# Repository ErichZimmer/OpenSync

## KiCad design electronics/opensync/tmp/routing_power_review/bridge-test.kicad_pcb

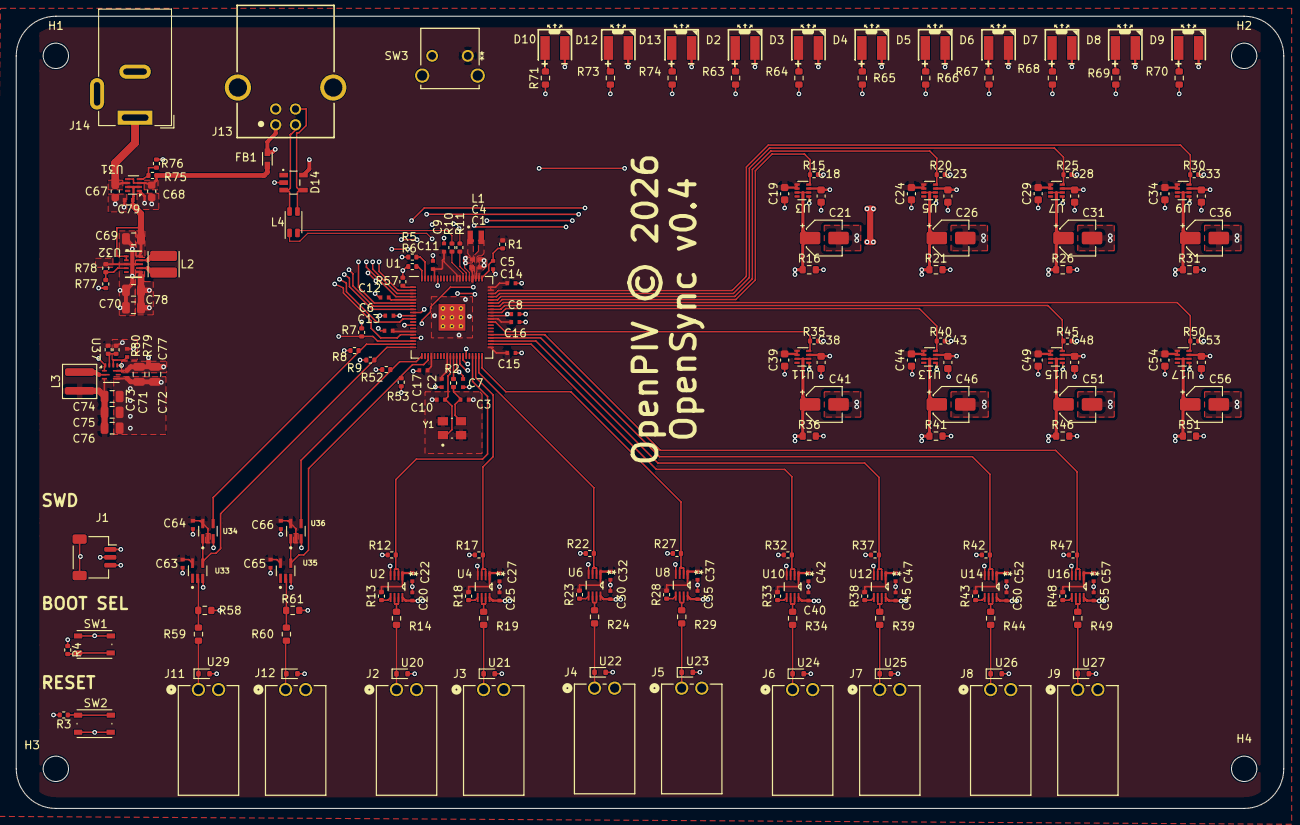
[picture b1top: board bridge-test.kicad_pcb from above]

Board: 4 copper layers, 160.0 x 100.0 mm, 221 parts (0 on the bottom side), 114 nets.

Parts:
C1, C4, C5: 4.7u; C_0402_1005Metric_small_pads
C2, C3: 15p; C_0402_1005Metric_small_pads
C6, C7, C8, C9, C10, C11, C12, C13, C14, C15, C16, C17, C20, C22, C25, C27, C30, C32, C35, C37, C40, C42, C45, C47, C50, C52, C55, C57, C63, C64, C65, C66, C79: 100n; C_0402_1005Metric_small_pads
C18, C19, C23, C24, C28, C29, C33, C34, C38, C39, C43, C44, C48, C49, C53, C54, C67, C68: 1u; C_0603_1608Metric
C21, C26, C31, C36, C41, C46, C51, C56: 22u; CP_Elec_4x5.4
C69, C71, C72: 10u; C_0805_2012Metric
C70, C74, C75, C76, C78: 22u; C_0805_2012Metric
C73: 2.2n; C_0402_1005Metric_small_pads
C77: 470n; C_0402_1005Metric_small_pads
D2, D3, D4, D5, D6, D7, D8, D9, D10, D12, D13: LED; LED-SMD_L4.0-W3.6_A67F-U2BA-1-3A4B-30-R33
D14: 5V; WE-TVS_SOT23-5L
FB1: 0603_W2.6_742792641; FB_Wurth_WE-CBF-0603_W2.6
H1, H2, H3, H4: MountingHole; MountingHole_3.2mm_M3_ISO7380
J1: SM03B-SRSS-TB; JST_SH_SM03B-SRSS-TB_1x03-1MP_P1.00mm_Horizontal
J2, J3, J4, J5, J6, J7, J8, J9, J11, J12: 705530001; CONN_705530001_02_MOL
J13: 61400416121
J14: Barrel_Jack_Switch; BarrelJack_Wuerth_6941xx301002
L1: 3.3u; L_pol_2016
L2: 470n; L_Wuerth_MAPI-3020
L3: 2.2u; L_Wuerth_MAPI-4020
L4: Choke_Wurth_WE-CNSW_744232090; L_CommonMode_Wurth_WE-CNSW-1206
R1: 33; R_0402_1005Metric
R2, R3, R4: 1k; R_0402_1005Metric
R5, R6, R7, R8, R9, R12, R15, R17, R20, R22, R25, R27, R30, R32, R35, R37, R40, R42, R45, R47, R50, R52, R53, R57: 10k; R_0402_1005Metric
R10, R11: 27; R_0402_1005Metric
R13, R18, R23, R28, R33, R38, R43, R48: 47k; R_0402_1005Metric
R14, R19, R24, R29, R34, R39, R44, R49: 39; R_0603_1608Metric
R16, R21, R26, R31, R36, R41, R46, R51, R58, R61: 10k; R_0603_1608Metric
R59, R60: 100; R_0603_1608Metric
R63, R64, R65, R66, R67, R68, R69, R70, R71, R73, R74: 470; R_0603_1608Metric
R75: 301k; R_0402_1005Metric
R76: 100k; R_0402_1005Metric
R77: 806k; R_0402_1005Metric
R78: 91k; R_0402_1005Metric
R79: 4.99k; R_0402_1005Metric
R80: 15.6k; R_0402_1005Metric
SW1, SW2: SW_Push; SW_Push_1P1T_NO_Vertical_Wuerth_434133025816
SW3: 2-1825027-0; SW2_1825027-G_TEC
U1: RP2354_80QFN; RP2350-QFN-80-1EP_10x10_P0.4mm_EP3.4x3.4mm_ThermalVias
U2, U4, U6, U8, U10, U12, U14, U16: SN74LVC2T45DCUR; DCU8
U3, U5, U7, U9, U11, U13, U15, U17, U31: TPS2116DRL; SOT-583-8
U20, U21, U22, U23, U24, U25, U26, U27, U29, U30: TPD1E05U06DYA; D_SOD-523
U32: TPS63802DLAR; DLA0010A
U33, U35: SN74LVC1G17DCKR; SOT65P210X110-5N
U34, U36: 74LVC1G86; SOT65P210X110-5N
U37: TPS62912; Texas_RPU0010A_VQFN-HR-10_2x2mm_P0.5mm
Y1: ABM8-272-T3; XTAL_ABM8-272-T3

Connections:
+1V1: C4.1, C6.1, C7.1, C8.1, L1.1, U1.10 (DVDD), U1.32 (DVDD), U1.51 (DVDD), U1.65 (VREG_FB)
+3V3: C1.1, C9.1, C10.1, C11.1, C12.1, C13.1, C14.1, C15.1, C16.1, C17.1, C19.2, C22.2, C24.2, C27.2, C29.2, C32.2, C34.2, C37.2, C39.2, C42.2, C44.2, C47.2, C49.2, C52.2, C54.2, C57.2, C63.1, C64.1, C65.1, C66.1, C74.2, C75.2, C76.2, L3.2, R1.1, R13.1, R18.1, R23.1, R28.1, R33.1, R38.1, R43.1, R48.1, R80.2, SW3.1, U1.5 (IOVDD), U1.15 (IOVDD), U1.24 (IOVDD), U1.29 (IOVDD), U1.41 (IOVDD), U1.50 (IOVDD), U1.59 (ADC_AVDD), U1.60 (IOVDD), U1.64 (VREG_VIN), U1.68 (USB_OTP_VDD), U1.69 (QSPI_IOVDD), U1.76 (IOVDD), U2.1 (VCCA), U3.5 (MODE), U3.6 (VIN2), U4.1 (VCCA), U5.5 (MODE), U5.6 (VIN2), U6.1 (VCCA), U7.5 (MODE), U7.6 (VIN2), U8.1 (VCCA), U9.5 (MODE), U9.6 (VIN2), U10.1 (VCCA), U11.5 (MODE), U11.6 (VIN2), U12.1 (VCCA), U13.5 (MODE), U13.6 (VIN2), U14.1 (VCCA), U15.5 (MODE), U15.6 (VIN2), U16.1 (VCCA), U17.5 (MODE), U17.6 (VIN2), U33.5 (VCC), U34.2, U34.5 (VCC), U35.5 (VCC), U36.2, U36.5 (VCC), U37.3 (VO)
+5V: C18.2, C23.2, C28.2, C33.2, C38.2, C43.2, C48.2, C53.2, C70.2, C71.2, C72.2, C73.2, C78.2, R77.2, U3.3 (VIN1), U5.3 (VIN1), U7.3 (VIN1), U9.3 (VIN1), U11.3 (VIN1), U13.3 (VIN1), U15.3 (VIN1), U17.3 (VIN1), U32.6 (VOUT), U37.1 (EN/SYNC), U37.6 (VIN), U37.10 (S-CONF)
/IN_G: R53.1, U1.23 (GPIO23), U35.4 (Y), U36.1
/IN_G_INV: R52.1, U1.21 (GPIO21), U36.4
/IN_T: R9.1, U1.20 (GPIO20), U33.4 (Y), U34.1
/IN_T_INV: R8.1, U1.19 (GPIO19), U34.4
/Indicator Panel/BTN_START: R7.1, SW3.2, U1.18 (GPIO18)
/Indicator Panel/LED_A: R70.1, U1.2 (GPIO5)
/Indicator Panel/LED_ACTIVE: R71.1, U1.17 (GPIO17)
/Indicator Panel/LED_B: R69.1, U1.3 (GPIO6)
/Indicator Panel/LED_C: R68.1, U1.4 (GPIO7)
/Indicator Panel/LED_D: R67.1, U1.6 (GPIO8)
/Indicator Panel/LED_E: R66.1, U1.7 (GPIO9)
/Indicator Panel/LED_F: R65.1, U1.8 (GPIO10)
/Indicator Panel/LED_G: R64.1, U1.9 (GPIO11)
/Indicator Panel/LED_GATE: R74.1, U1.13 (GPIO14)
/Indicator Panel/LED_H: R63.1, U1.11 (GPIO12)
/Indicator Panel/LED_TRIG: R73.1, U1.16 (GPIO16)
/Microcontroller Circuitry/QSPI_SS: R4.1, U1.75 (QSPI_SS)
/Microcontroller Circuitry/RUN: SW2.2, U1.35 (RUN)
/Microcontroller Circuitry/SIG_CLOCK: R6.2, U1.80 (GPIO3)
/Microcontroller Circuitry/SIG_GATE_INT: R57.2, U1.1 (GPIO4)
/Microcontroller Circuitry/SIG_T0: R5.2, U1.79 (GPIO2)
/Microcontroller Circuitry/SWCLK: J1.1, U1.33 (SWCLK)
/Microcontroller Circuitry/SWD: J1.3, U1.34 (SWD)
/Microcontroller Circuitry/USB_D+: L4.4, R10.1
/Microcontroller Circuitry/USB_D-: L4.1, R11.1
/Microcontroller Circuitry/VREG_LX: L1.2, U1.63 (VREG_LX)
/Microcontroller Circuitry/XIN: C2.2, U1.30 (XIN), Y1.1
/Microcontroller Circuitry/XOUT: R2.2, U1.31 (XOUT)
/OUT_A: R12.1, U1.37 (GPIO29), U2.2 (A1), U2.3 (A2)
/OUT_B: R17.1, U1.38 (GPIO30), U4.2 (A1), U4.3 (A2)
/OUT_C: R22.1, U1.39 (GPIO31), U6.2 (A1), U6.3 (A2)
/OUT_D: R27.1, U1.40 (GPIO32), U8.2 (A1), U8.3 (A2)
/OUT_E: R32.1, U1.42 (GPIO33), U10.2 (A1), U10.3 (A2)
/OUT_F: R37.1, U1.43 (GPIO34), U12.2 (A1), U12.3 (A2)
/OUT_G: R42.1, U1.44 (GPIO35), U14.2 (A1), U14.3 (A2)
/OUT_H: R47.1, U1.45 (GPIO36), U16.2 (A1), U16.3 (A2)
/Output Channel 1/VOUT: C20.2, C21.1, R16.1, U2.8 (VCCB), U3.2 (VOUT), U3.7 (VOUT)
/Output Channel 2/VOUT: C25.2, C26.1, R21.1, U4.8 (VCCB), U5.2 (VOUT), U5.7 (VOUT)
/Output Channel 3/VOUT: C30.2, C31.1, R26.1, U6.8 (VCCB), U7.2 (VOUT), U7.7 (VOUT)
/Output Channel 4/VOUT: C35.2, C36.1, R31.1, U8.8 (VCCB), U9.2 (VOUT), U9.7 (VOUT)
/Output Channel 5/VOUT: C40.2, C41.1, R36.1, U10.8 (VCCB), U11.2 (VOUT), U11.7 (VOUT)
/Output Channel 6/VOUT: C45.2, C46.1, R41.1, U12.8 (VCCB), U13.2 (VOUT), U13.7 (VOUT)
/Output Channel 7/VOUT: C50.2, C51.1, R46.1, U14.8 (VCCB), U15.2 (VOUT), U15.7 (VOUT)
/Output Channel 8/VOUT: C55.2, C56.1, R51.1, U16.8 (VCCB), U17.2 (VOUT), U17.7 (VOUT)
/Power Interface/VDC: C67.2, J14.1, U31.6 (VIN2)
/Power Interface/VOUT: C69.2, C79.1, U31.2 (VOUT), U31.7 (VOUT), U32.1 (EN), U32.2 (MODE), U32.10 (VIN)
/USB Interface/VBUS_RAW: D14.5 (VDD), FB1.2, J13.1 (VBUS)
/VSEL_A: R15.1, U1.55 (GPIO44_ADC4), U3.4 (PR1)
/VSEL_B: R20.1, U1.56 (GPIO45_ADC5), U5.4 (PR1)
/VSEL_C: R25.1, U1.57 (GPIO46_ADC6), U7.4 (PR1)
/VSEL_D: R30.1, U1.58 (GPIO47_ADC7), U9.4 (PR1)
/VSEL_E: R35.1, U1.49 (GPIO40_ADC0), U11.4 (PR1)
/VSEL_F: R40.1, U1.52 (GPIO41_ADC1), U13.4 (PR1)
/VSEL_G: R45.1, U1.53 (GPIO42_ADC2), U15.4 (PR1)
/VSEL_H: R50.1, U1.54 (GPIO43_ADC3), U17.4 (PR1)
GND: C1.2, C2.1, C3.1, C4.2, C5.2, C6.2, C7.2, C8.2, C9.2, C10.2, C11.2, C12.2, C13.2, C14.2, C15.2, C16.2, C17.2, C18.1, C19.1, C20.1, C21.2, C22.1, C23.1, C24.1, C25.1, C26.2, C27.1, C28.1, C29.1, C30.1, C31.2, C32.1, C33.1, C34.1, C35.1, C36.2, C37.1, C38.1, C39.1, C40.1, C41.2, C42.1, C43.1, C44.1, C45.1, C46.2, C47.1, C48.1, C49.1, C50.1, C51.2, C52.1, C53.1, C54.1, C55.1, C56.2, C57.1, C63.2, C64.2, C65.2, C66.2, C67.1, C68.1, C69.1, C70.1, C71.1, C72.1, C73.1, C74.1, C75.1, C76.1, C77.1, C78.1, C79.2, D2.1 (K), D3.1 (K), D4.1 (K), D5.1 (K), D6.1 (K), D7.1 (K), D8.1 (K), D9.1 (K), D10.1 (K), D12.1 (K), D13.1 (K), D14.2 (GND), J1.2, J1.MP (MountPin), J2.2, J3.2, J4.2, J5.2, J6.2, J7.2, J8.2, J9.2, J11.2, J12.2, J13.4 (GND), J13.S1, J13.S2, J14.3, R3.2, R5.1, R6.1, R7.2, R8.2, R9.2, R12.2, R15.2, R16.2, R17.2, R20.2, R21.2, R22.2, R25.2, R26.2, R27.2, R30.2, R31.2, R32.2, R35.2, R36.2, R37.2, R40.2, R41.2, R42.2, R45.2, R46.2, R47.2, R50.2, R51.2, R52.2, R53.2, R57.1, R58.2, R61.2, R76.2, R78.2, R79.2, SW1.1, U1.62 (VREG_PGND), U1.81 (GND), U2.4 (GND), U3.1 (GND), U4.4 (GND), U5.1 (GND), U6.4 (GND), U7.1 (GND), U8.4 (GND), U9.1 (GND), U10.4 (GND), U11.1 (GND), U12.4 (GND), U13.1 (GND), U14.4 (GND), U15.1 (GND), U16.4 (GND), U17.1 (GND), U20.2 (GND), U21.2 (GND), U22.2 (GND), U23.2 (GND), U24.2 (GND), U25.2 (GND), U26.2 (GND), U27.2 (GND), U29.2 (GND), U30.2 (GND), U31.1 (GND), U32.3 (AGND), U32.8 (GND), U33.3 (GND), U34.3 (GND), U35.3 (GND), U36.3 (GND), U37.4 (PGND), U37.7 (PSNS), Y1.2 (GND), Y1.4 (GND)
unnamed: C3.2, R2.1, Y1.3
unnamed: D2.2 (A), R63.2
unnamed: D3.2 (A), R64.2
unnamed: D4.2 (A), R65.2
unnamed: D5.2 (A), R66.2
unnamed: D6.2 (A), R67.2
unnamed: D7.2 (A), R68.2
unnamed: D8.2 (A), R69.2
unnamed: D9.2 (A), R70.2
unnamed: D10.2 (A), R71.2
unnamed: D12.2 (A), R73.2
unnamed: D13.2 (A), R74.2
unnamed: D14.3 (I/O_1), J13.2 (D-), L4.2
unnamed: D14.4 (I/O_2), J13.3 (D+), L4.3
unnamed: R3.1, SW2.1
unnamed: R4.2, SW1.2
unnamed: R11.2, U1.66 (USB_DM)
unnamed: R10.2, U1.67 (USB_DP)
unnamed: C5.1, R1.2, U1.61 (VREG_AVDD)
unnamed: R14.1, U2.6 (B2), U2.7 (B1)
unnamed: R13.2, U2.5 (DIR)
unnamed: R19.1, U4.6 (B2), U4.7 (B1)
unnamed: R18.2, U4.5 (DIR)
unnamed: R24.1, U6.6 (B2), U6.7 (B1)
unnamed: R23.2, U6.5 (DIR)
unnamed: R29.1, U8.6 (B2), U8.7 (B1)
unnamed: R28.2, U8.5 (DIR)
unnamed: R34.1, U10.6 (B2), U10.7 (B1)
unnamed: R33.2, U10.5 (DIR)
unnamed: R39.1, U12.6 (B2), U12.7 (B1)
unnamed: R38.2, U12.5 (DIR)
unnamed: R44.1, U14.6 (B2), U14.7 (B1)
unnamed: R43.2, U14.5 (DIR)
unnamed: R49.1, U16.6 (B2), U16.7 (B1)
unnamed: R48.2, U16.5 (DIR)
unnamed: J2.1, R14.2, U20.1 (I/O)
unnamed: J3.1, R19.2, U21.1 (I/O)
unnamed: J4.1, R24.2, U22.1 (I/O)
unnamed: J5.1, R29.2, U23.1 (I/O)
unnamed: J6.1, R34.2, U24.1 (I/O)
unnamed: J7.1, R39.2, U25.1 (I/O)
unnamed: J8.1, R44.2, U26.1 (I/O)
unnamed: J9.1, R49.2, U27.1 (I/O)
unnamed: J11.1, R59.1, U29.1 (I/O)
unnamed: J12.1, R60.1, U30.1 (I/O)
unnamed: R75.2, R76.1, U31.4 (PR1)
unnamed: R77.1, R78.1, U32.4 (FB)
unnamed: L2.1, U32.9 (L1)
unnamed: L2.2, U32.7 (L2)
unnamed: R58.1, R59.2, U33.2 (A)
unnamed: R60.2, R61.1, U35.2 (A)
unnamed: R79.1, R80.1, U37.9 (FB)
unnamed: C77.2, U37.8 (NR/SS)
unnamed: L3.1, U37.2 (SW)
VBUS: C68.2, FB1.1, R75.1, U31.3 (VIN1), U31.5 (MODE)

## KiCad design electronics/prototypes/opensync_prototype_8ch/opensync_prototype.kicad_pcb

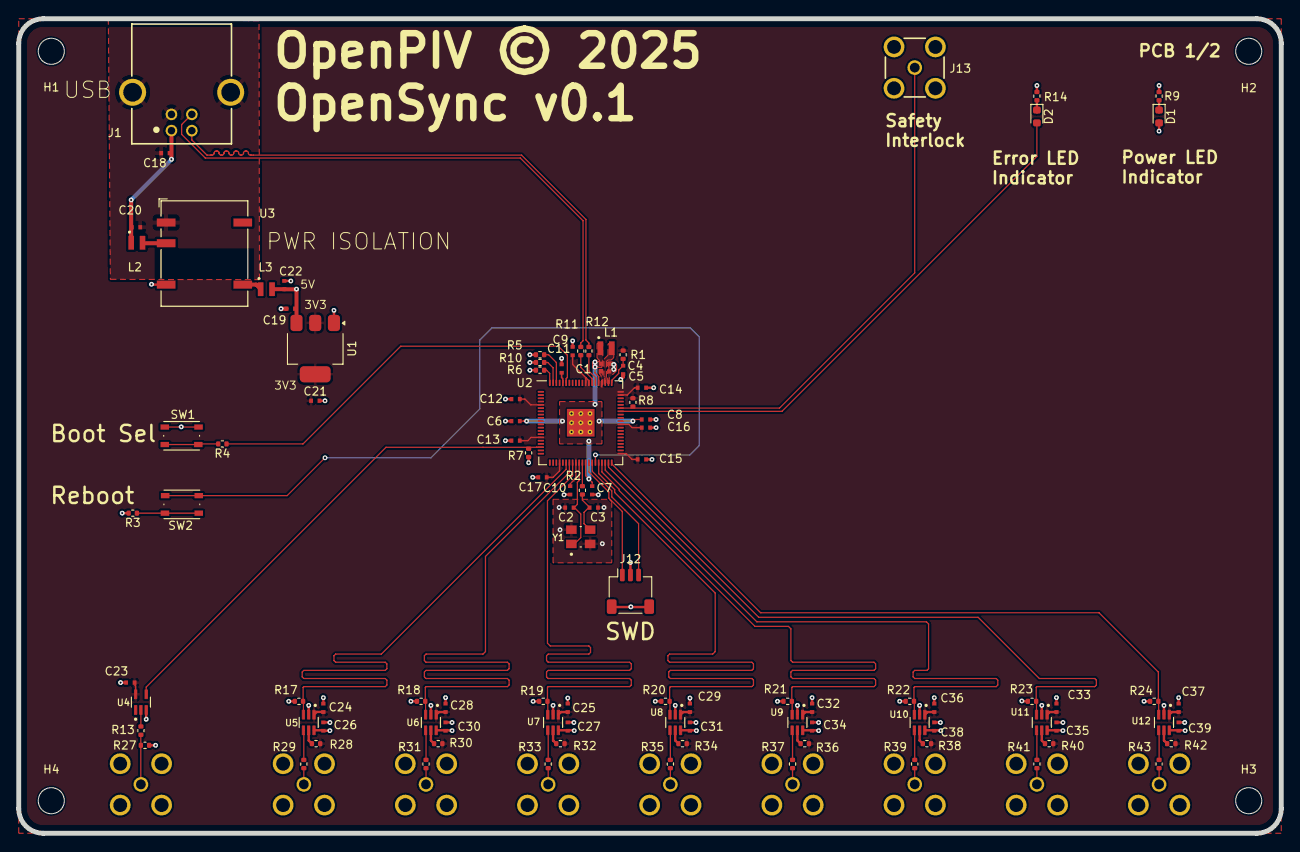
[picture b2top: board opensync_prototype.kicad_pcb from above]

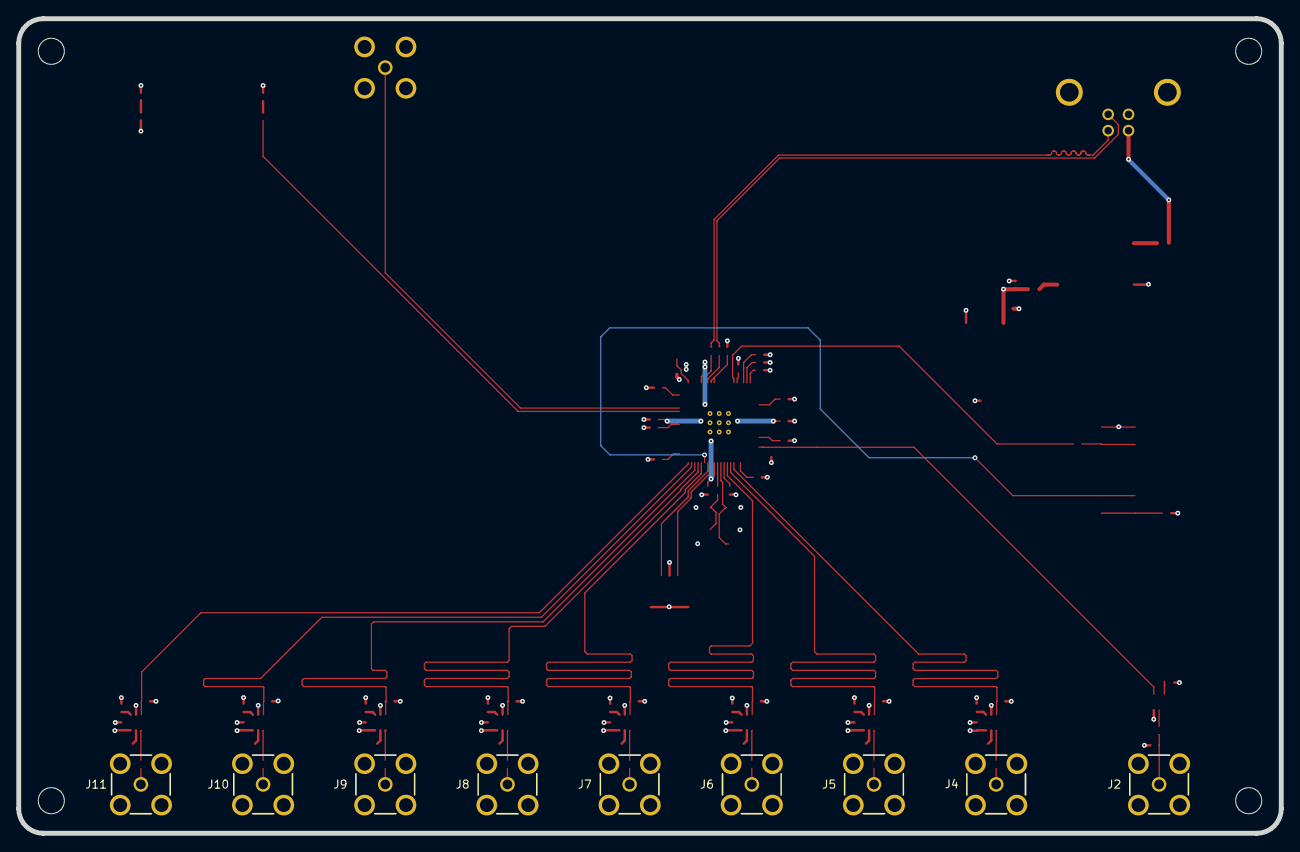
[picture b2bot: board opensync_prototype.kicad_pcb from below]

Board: 4 copper layers, 155.0 x 100.0 mm, 114 parts (9 on the bottom side), 65 nets.

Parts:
C1, C4, C5, C7, C20: 4.7u; C_0402_1005Metric_small_pads
C2, C3: C; C_0402_1005Metric_small_pads
C6, C8, C9, C10, C11, C12, C13, C14, C15, C16, C17, C23, C24, C25, C26, C27, C28, C29, C30, C31, C32, C33, C34, C35, C36, C37, C38, C39: 100n; C_0402_1005Metric_small_pads
C18, C19, C21, C22: 10u; C_0402_1005Metric_small_pads
D1, D2: LED; LED_0603_1608Metric
H1, H2, H3, H4: MountingHole; MountingHole_3.2mm_M3_ISO7380
J1: 61400416121
J2, J4, J5, J6, J7, J8, J9, J10, J11, J13: 61611042121502
J12: SM03B-SRSS-TB; JST_SH_SM03B-SRSS-TB_1x03-1MP_P1.00mm_Horizontal
L1: 3.3u; L_pol_2016
L2: 15u; L_pol_2016
L3: 22u; L_pol_2016
R1: 33; R_0402_1005Metric
R2, R3, R4: 1k; R_0402_1005Metric
R5, R6, R7, R10, R17, R18, R19, R20, R21, R22, R23, R24: 10k; R_0402_1005Metric
R8, R27, R28, R30, R32, R34, R36, R38, R40, R42: 47k; R_0402_1005Metric
R9: 169; R_0402_1005Metric
R11, R12: 27; R_0402_1005Metric
R13: 470; R_0402_1005Metric
R14: 100; R_0402_1005Metric
R29, R31, R33, R35, R37, R39, R41, R43: 49.9; R_0402_1005Metric
SW1, SW2: SW_Push; SW_Push_1P1T_NO_Vertical_Wuerth_434133025816
U1: NCP1117-3.3_SOT223; SOT-223-3_TabPin2
U2: RP2354_80QFN; RP2350-QFN-80-1EP_10x10_P0.4mm_EP3.4x3.4mm_ThermalVias
U3: NXE2S0505MC; Converter_DCDC_Murata_NXExSxxxxMC_SMD
U4: SN74LVC1G17DCKR; SOT65P210X110-5N
U5, U6, U7, U8, U9, U10, U11, U12: SN74LVC1T45DCKR; SOT65P210X110-6N
Y1: ABM8-272-T3; XTAL_ABM8-272-T3

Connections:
+1V1: C4.1, C6.1, C7.1, C8.1, L1.1, U2.10 (DVDD), U2.32 (DVDD), U2.51 (DVDD), U2.65 (VREG_FB)
+3V3: C1.1, C9.1, C10.1, C11.1, C12.1, C13.1, C14.1, C15.1, C16.1, C17.1, C21.1, C23.1, C24.1, C25.1, C28.1, C29.1, C32.1, C33.1, C36.1, C37.1, R1.1, R8.1, R28.1, R30.1, R32.1, R34.1, R36.1, R38.1, R40.1, R42.1, U1.2 (VO), U2.5 (IOVDD), U2.15 (IOVDD), U2.24 (IOVDD), U2.29 (IOVDD), U2.41 (IOVDD), U2.50 (IOVDD), U2.59 (ADC_AVDD), U2.60 (IOVDD), U2.64 (VREG_VIN), U2.68 (USB_OTP_VDD), U2.69 (QSPI_IOVDD), U2.76 (IOVDD), U4.5 (VCC), U5.1 (VCCA), U6.1 (VCCA), U7.1 (VCCA), U8.1 (VCCA), U9.1 (VCCA), U10.1 (VCCA), U11.1 (VCCA), U12.1 (VCCA)
+5V: C19.1, C22.1, C26.1, C27.1, C30.1, C31.1, C34.1, C35.1, C38.1, C39.1, D1.2 (A), L3.2, U1.3 (VI), U5.6 (VCCB), U6.6 (VCCB), U7.6 (VCCB), U8.6 (VCCB), U9.6 (VCCB), U10.6 (VCCB), U11.6 (VCCB), U12.6 (VCCB)
/Microcontroller and Ext. Clock/CLOCK_1: R5.2, U2.78 (GPIO1)
/Microcontroller and Ext. Clock/CLOCK_2: R10.2, U2.79 (GPIO2)
/Microcontroller and Ext. Clock/CLOCK_3: R6.2, U2.80 (GPIO3)
/Microcontroller and Ext. Clock/ERROR_LED: D2.2 (A), U2.54 (GPIO43_ADC3)
/Microcontroller and Ext. Clock/OUTPUT_1: R17.1, U2.26 (GPIO25), U5.3 (A)
/Microcontroller and Ext. Clock/OUTPUT_2: R18.1, U2.27 (GPIO26), U6.3 (A)
/Microcontroller and Ext. Clock/OUTPUT_3: R19.1, U2.28 (GPIO27), U7.3 (A)
/Microcontroller and Ext. Clock/OUTPUT_4: R20.1, U2.36 (GPIO28), U8.3 (A)
/Microcontroller and Ext. Clock/OUTPUT_5: R21.1, U2.37 (GPIO29), U9.3 (A)
/Microcontroller and Ext. Clock/OUTPUT_6: R22.1, U2.38 (GPIO30), U10.3 (A)
/Microcontroller and Ext. Clock/OUTPUT_7: R23.1, U2.39 (GPIO31), U11.3 (A)
/Microcontroller and Ext. Clock/OUTPUT_8: R24.1, U2.40 (GPIO32), U12.3 (A)
/Microcontroller and Ext. Clock/QSPI_SS: R4.1, U2.75 (QSPI_SS)
/Microcontroller and Ext. Clock/RUN: SW2.2, U2.35 (RUN)
/Microcontroller and Ext. Clock/SAFETY_INTERLOCK: J13.1, R8.2, U2.55 (GPIO44_ADC4)
/Microcontroller and Ext. Clock/SWCLK: J12.1, U2.33 (SWCLK)
/Microcontroller and Ext. Clock/SWD: J12.3, U2.34 (SWD)
/Microcontroller and Ext. Clock/TRIGGER_1: R7.1, U2.18 (GPIO18), U4.4 (Y)
/Microcontroller and Ext. Clock/VREG_LX: L1.2, U2.63 (VREG_LX)
/Microcontroller and Ext. Clock/XIN: C2.2, U2.30 (XIN), Y1.1
/Microcontroller and Ext. Clock/XOUT: R2.2, U2.31 (XOUT)
/Power and Data/USB_D+: J1.3 (D+), R11.1
/Power and Data/USB_D-: J1.2 (D-), R12.1
GND: C1.2, C2.1, C3.1, C4.2, C5.2, C6.2, C7.2, C8.2, C9.2, C10.2, C11.2, C12.2, C13.2, C14.2, C15.2, C16.2, C17.2, C19.2, C21.2, C22.2, C23.2, C24.2, C25.2, C26.2, C27.2, C28.2, C29.2, C30.2, C31.2, C32.2, C33.2, C34.2, C35.2, C36.2, C37.2, C38.2, C39.2, J2.2, J2.3, J2.4, J2.5, J4.2, J4.3, J4.4, J4.5, J5.2, J5.3, J5.4, J5.5, J6.2, J6.3, J6.4, J6.5, J7.2, J7.3, J7.4, J7.5, J8.2, J8.3, J8.4, J8.5, J9.2, J9.3, J9.4, J9.5, J10.2, J10.3, J10.4, J10.5, J11.2, J11.3, J11.4, J11.5, J12.2, J12.MP (MountPin), J13.2, J13.3, J13.4, J13.5, R3.2, R5.1, R6.1, R7.2, R9.1, R10.1, R14.1, R17.2, R18.2, R19.2, R20.2, R21.2, R22.2, R23.2, R24.2, R27.2, SW1.1, U1.1 (GND), U2.62 (VREG_PGND), U2.81 (GND), U3.7 (-VOUT), U4.3 (GND), U5.2 (GND), U6.2 (GND), U7.2 (GND), U8.2 (GND), U9.2 (GND), U10.2 (GND), U11.2 (GND), U12.2 (GND), Y1.2 (GND), Y1.4 (GND)
GND_BUS: C18.2, C20.1, J1.4 (GND), J1.S1, J1.S2, U3.1 (-VIN)
unnamed: C3.2, R2.1, Y1.3
unnamed: D1.1 (K), R9.2
unnamed: D2.1 (K), R14.2
unnamed: J2.1, R13.1, R27.1
unnamed: J4.1, R29.2
unnamed: J5.1, R31.2
unnamed: J6.1, R33.2
unnamed: J7.1, R35.2
unnamed: J8.1, R37.2
unnamed: J9.1, R39.2
unnamed: J10.1, R41.2
unnamed: J11.1, R43.2
unnamed: R3.1, SW2.1
unnamed: R4.2, SW1.2
unnamed: R12.2, U2.66 (USB_DM)
unnamed: R11.2, U2.67 (USB_DP)
unnamed: C5.1, R1.2, U2.61 (VREG_AVDD)
unnamed: L2.2, U3.3 (+VIN)
unnamed: L3.1, U3.8 (+VOUT)
unnamed: R13.2, U4.2 (A)
unnamed: R29.1, U5.4 (B)
unnamed: R28.2, U5.5 (DIR)
unnamed: R31.1, U6.4 (B)
unnamed: R30.2, U6.5 (DIR)
unnamed: R33.1, U7.4 (B)
unnamed: R32.2, U7.5 (DIR)
unnamed: R35.1, U8.4 (B)
unnamed: R34.2, U8.5 (DIR)
unnamed: R37.1, U9.4 (B)
unnamed: R36.2, U9.5 (DIR)
unnamed: R39.1, U10.4 (B)
unnamed: R38.2, U10.5 (DIR)
unnamed: R41.1, U11.4 (B)
unnamed: R40.2, U11.5 (DIR)
unnamed: R43.1, U12.4 (B)
unnamed: R42.2, U12.5 (DIR)
VBUS: C18.1, C20.2, J1.1 (VBUS), L2.1

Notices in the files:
electronics/opensync/tmp/routing_power_review/bridge-test.kicad_pcb:
OpenPIV © 2026
electronics/prototypes/opensync_prototype_8ch/opensync_prototype.kicad_pcb:
OpenPIV © 2025
